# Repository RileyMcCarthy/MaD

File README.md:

# MaD — Low-Cost Open-Source Tensile Testing Machine

A relatively low-cost (**< $4,000**), portable, spray-resistant, user-modifiable,
open-source **uniaxial tensile testing machine** designed for low-modulus
elastomeric and biologic materials.

**📖 Documentation: <https://rileymccarthy.github.io/MaD/>** ·
**🚀 Run the control app: <https://rileymccarthy.github.io/MaD/app/>** (Chrome/Edge)

> The full guides — first-time setup, every UI screen with screenshots, the
> architecture, and developer/reference material — live on the
> [documentation site](https://rileymccarthy.github.io/MaD/). This README is the
> quick map.

## Specifications

| Parameter | Range |
|---|---|
| Strain Rate | 0 – 2 m/s |
| Force Measurement | 1 – 10 N |
| Gauge Length | 10 – 150 mm |
| Strain Length | 0 – 500 mm |
| Data Rate | 1000 samples/sec |

## The control app runs in your browser

The control app — **Control** — is a frontend-only Progressive Web App.
There is **nothing to install**: the browser talks straight to the Propeller 2
over the **Web Serial API**, and the protocol logic runs as **WebAssembly**
compiled from the same Rust core used by the firmware tooling and the test rig.

Open **<https://rileymccarthy.github.io/MaD/app/>** in Chrome or Edge, connect
over USB, and run a test. See the
[getting started guide](https://rileymccarthy.github.io/MaD/getting-started/).

> **Chromium-only:** Web Serial and the File System Access API are available only
> in Chrome/Edge on desktop.

## Repository structure

```
MaD/
├── Firmware/MaDCore/        Embedded C for the Propeller 2 (APP/DEV/IO/Library/HAL/HW)
├── Software/
│   └── Control/      Browser control app (Web Serial + WASM) — the app you ship
├── Protocol/                Schema + toolchain + Rust codec crate
│   ├── MaDProtocol.yaml     Single source-of-truth schema
│   ├── rust/                The `protocol` crate — generated Rust codec (SIL workspace member)
│   └── ProtoEmb/            ⎘ submodule → github.com/RileyMcCarthy/protoemb (YAML→C/TS/Rust codegen + runtime)
├── SIL/                     Software-in-the-loop test rig (Rust workspace)
│   ├── embsim/              ⎘ submodule → github.com/RileyMcCarthy/embsim (reusable SIL framework)
│   ├── models/              MaD physics models (gantry, sample, strain gauge)
│   ├── p2core/              The Propeller 2 instruction-set simulator (ISS)
│   ├── p2iss/               The ISS as an embsim component
│   ├── mad-catalog/         MaD's embsim kinds (carrier, add-on, ISS, machine); mad*.toml are the machine's projects
│   └── mad-runner/          The embsim command over MaD's kinds
├── Vibes/                   ⎘ submodule → github.com/RileyMcCarthy/vibes (behaviour ledger tool; the ledger is behaviours.jsonl)
├── Hardware/                KiCad PCB designs (EdgeBoard, DS2Addon)
└── docs/  +  mkdocs.yml     The documentation site
```

> Three components are **git submodules** (they are standalone open-source
> libraries): [`Protocol/ProtoEmb`](https://github.com/RileyMcCarthy/protoemb),
> [`SIL/embsim`](https://github.com/RileyMcCarthy/embsim) and
> [`Vibes`](https://github.com/RileyMcCarthy/vibes). Clone with
> `git clone --recurse-submodules`, or run
> `git submodule update --init --recursive` in an existing checkout.

## How it fits together

A single YAML schema (`Protocol/MaDProtocol.yaml`) generates the encode/decode
code for the firmware (C), the app (TypeScript + WASM), and the test rig (Rust),
so every layer agrees on the wire format byte-for-byte. The app and firmware speak
this **ProtoEmb** binary protocol over serial; motion profiles compile to G-code
that the firmware plays back from its SD card.

See [How it works](https://rileymccarthy.github.io/MaD/how-it-works/) for the
architecture with diagrams.

## Quick start

### Use the app
Open <https://rileymccarthy.github.io/MaD/app/> in Chrome/Edge — no install.

### Run the app from source
```bash
cd Software/Control
npm install
npm run build:wasm        # compile the Rust protocol core → src/wasm/
npm run generate:proto    # generate the TS codec from the YAML schema
npm run app               # opens your browser; connect on the control port via Web Serial
```

### Build the firmware
```bash
cd Firmware/MaDCore
pio run -e MaD                 # the firmware: hardware and the SIL run this image
pio run -e MaD -t upload       # flash a connected board through J1 (the programming port)
pio test -e native_test        # unit tests
pio check -e MaD --fail-on-defect=medium --fail-on-defect=high  # MISRA (medium+high)
```

The machine has two serial ports: the **control port** (the secondary serial on
P30/P32, J4 on the Edge carrier v0.3), which carries the protocol and never
resets the chip, and the **programming port** (J1, or the P2-EVAL's own USB),
whose DTR resets the chip for flashing and which carries the debug log.

### Run the full simulation (no hardware)
```bash
cd SIL
make test         # build the P2 image + the workspace, run the Rust test suite
make playground   # the machine's project + the app in a Chrome window on the board's clock
make e2e          # the e2e suite on the machine's project, mad-cosim.toml (SCENARIOS=… for a subset)
```

### Regenerate the protocol
After editing `Protocol/MaDProtocol.yaml`, regenerate all three targets so they
stay in lock-step (the firmware also regenerates its C target on every build):
```bash
# from repo root
python3 ./Protocol/ProtoEmb/core/generate.py --schema ./Protocol/MaDProtocol.yaml --target c  --output ./Firmware/MaDCore/src/Generated         --templates ./Protocol/ProtoEmb/core/templates
python3 ./Protocol/ProtoEmb/core/generate.py --schema ./Protocol/MaDProtocol.yaml --target ts --output ./Software/Control/src/protocol/generated --templates ./Protocol/ProtoEmb/core/templates
python3 ./Protocol/ProtoEmb/core/generate.py --schema ./Protocol/MaDProtocol.yaml --target rs --output ./Protocol/rust/src/generated          --templates ./Protocol/ProtoEmb/core/templates
```

## Documentation

| If you want to… | Go to |
|---|---|
| Set up a machine and run your first test | [Getting started](https://rileymccarthy.github.io/MaD/getting-started/) |
| Learn every screen | [User guide](https://rileymccarthy.github.io/MaD/user-guide/) |
| Understand the design | [How it works](https://rileymccarthy.github.io/MaD/how-it-works/) |
| Build & contribute | [Developer guide](https://rileymccarthy.github.io/MaD/dev/) |
| Look up the protocol / G-code / formats | [Protocol messages](https://rileymccarthy.github.io/MaD/dev/protocol-messages/) · [G-code](https://rileymccarthy.github.io/MaD/dev/gcode/) · [File formats](https://rileymccarthy.github.io/MaD/user-guide/file-formats/) |

To work on the docs locally:
```bash
pip install -r docs/requirements.txt
mkdocs serve     # http://127.0.0.1:8000
```

## CI/CD & releases

GitHub Actions builds and tests on every push/PR (`.github/workflows/ci.yml`) and
deploys the docs + app to GitHub Pages (`.github/workflows/pages.yml`). Releases
are cut with version tags:

```bash
Software/Control/scripts/release.sh patch --no-tag   # bump package.json, then PR
Software/Control/scripts/release.sh --publish        # tag origin/main as madcontrol-vX.Y.Z
git tag firmware-v1.0.0 && git push origin firmware-v1.0.0   # firmware binaries
git tag hardware-v1.0.0 && git push origin hardware-v1.0.0   # hardware manufacturing files
```

## License

MIT

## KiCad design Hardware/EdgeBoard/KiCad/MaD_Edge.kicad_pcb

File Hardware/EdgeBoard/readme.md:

# MaD EdgeBoard

The **EdgeBoard** is the main controller PCB for the MaD tensile tester. It hosts
the **Parallax Propeller 2** microcontroller and carries all of the machine's I/O.

The current design is **revision v0.3** (2026-10). The revision is printed on the
silkscreen ("Rev v0.3", under the MaD logo) and in every title block. Boards made
from earlier files carry no revision text; the changelog below lists what differs.

## What's on the board

- **Propeller 2** module socket (the firmware in
  [`Firmware/MaDCore`](../../Firmware/MaDCore) runs here). The machine uses a
  **P2-EC32MB** module; see [P2 module pins](#p2-module-pins).
- **Servo drive interface** (J21): isolated STEP/DIR line drivers, enable, ready.
- **Encoder input** (J20): isolated quadrature receiver for the drive's encoder.
- **Endstops** and the **door interlock** / e-stop chain (J11-J18, current-loop
  inputs through optocouplers).
- **Control port: J4.** The control app talks to the P2 on P30 (RX) / P32 (TX),
  isolated through IC2, at 2,000,000 baud. The carrier has no USB-to-serial chip
  of its own.
- **Programming port: J1.** A Parallax Prop Plug on J1 (P62/P63/RESn/GND,
  silkscreen `G|RES|RX|TX`) flashes the firmware and carries its debug log. It
  does not carry the protocol.
- Header for the [DS2 Addon](../DS2Addon/readme.md) force-gauge interface.

## Encoder input (J20) and its jumpers

U25 is a 5 V RS-422 receiver (AM26C32). Every channel has a header jumper that
ties its minus input to **ENC_REF**, a 2.5 V reference made from SC_5V by
R43/R44 (2.2 kΩ each) and decoupled by C31:

| Jumper | Ties | Channel | U25 pins | P2 pin |
|---|---|---|---|---|
| JP2 `A` | A- (J20.2) to ENC_REF | A | 2/1 | P9 |
| JP3 `B` | B- (J20.4) to ENC_REF | B | 6/7 | P10 |
| JP6 `Z` | Z- (J20.8) to ENC_REF | Z (index) | 14/15 | P12 |
| JP5 `ZI` | ZI- (J20.10) to ENC_REF | ZI | 10/9 | P11 |

R40/R41/R42 (2.2 kΩ) pull A+, B+ and Z+ up to SC_5V. ZI+ has no pull-up.

**Settings by encoder type** (the silkscreen between the jumpers reads
`OC: A B Z`, the three to fit for an open-collector encoder):

- **RS-422 line-driver encoder** (A/A-, B/B-, Z/Z-): leave **all four jumpers
  open**. Wire A±, B±, Z± (and ZI± if it has a second index) to J20, and its 0 V to
  J20.5. A shunt here would short the driver's minus output to ENC_REF, which ties
  all four minus legs together.
- **Single-ended NPN open-collector encoder** (A, B, Z; for example the Omron
  E6B2-CWZ6C and its clones, such as the Taiss on this machine): fit shunts on
  **JP2, JP3 and JP6**. Wire A to J20.1, B to J20.3, Z to J20.7, and the encoder 0 V
  to J20.5. Leave JP5 open.
  - The encoder must be a true open collector, with **no internal pull-up**. A
    "voltage output" NPN encoder pulls its outputs up to its own supply.
  - A, B and Z read **inverted** on P9/P10/P12. The output sinks while active, so
    the Z index pulse is **active-low** on P12 (inferred: the receiver output is
    low whenever the + input is below ENC_REF). Inverting both A and B keeps the
    count direction.
- **Single-ended push-pull 0/5 V (TTL) encoder:** as for open collector. The
  pull-ups are harmless. Fit JP5 too if a second index is wired to ZI+.
- **Not supported: any encoder whose outputs swing above 5 V.** That includes
  push-pull HTL outputs and voltage-output NPN outputs on a 12-24 V supply. The
  silkscreen under J25 reads `ENC OUT 5V MAX`.
  - U25's A/B inputs are rated -11 V to +14 V absolute maximum, with a ±7 V
    common-mode range (read: TI SLLS104M §5.1 and §5.3, p.4). A 24 V output
    exceeds that.
  - It also pushes current back into the drive's 5 V through the 2.2 kΩ
    pull-ups: (24 - 5) V / 2.2 kΩ = 8.6 mA per line (inferred).

**Encoder supply (J25, `VIN +V 0V`).** J20 has no supply pin; all ten pins are
used. The encoder side of the board has only SC_5V, which comes from the drive
through J21.1. J25 is a pass-through for an external supply:

- J25.1 `VIN`: the external supply, **at the voltage the encoder is rated for**.
  For example, the Taiss is reported to need at least 7 V, and a 5 V RS-422
  encoder needs 5 V.
  - VIN may be up to 30 V, F1's rating (read: LUTE 1206L datasheet, Revision 2020,
    p.2).
- J25.2 `+V`: to the encoder's V+, through F1 (PTC, 0.20 A hold).
- J25.3 `0V`: the supply 0 V, tied to the encoder ground (EN_GND).
- **Use a supply that is isolated from the carrier's V_IN.** J25.3 is EN_GND, the
  drive side of IC14/IC16. A supply shared with V_IN returns to the carrier's GND,
  which joins the two grounds and bypasses the isolators (inferred from the
  netlist: V_IN returns to GND).

The pin order keeps VIN and 0 V apart, so one stray shunt cannot short the supply.

**Load on the drive's 5 V (SC_5V, J21.1).** The carrier draws up to about 45 mA
from it (inferred: sum of datasheet maxima at 5.5 V). On top of that, U24 sources
whatever the drive's STEP/DIR inputs draw. Check the total against the drive's
5 V output rating; the repo does not record the drive model.

| Load | Max current | Source |
|---|---|---|
| U25 AM26C32 | 15 mA | SLLS104M §5.6, p.5 |
| IC16 side 1 | 8 mA | ISO6740 DC, SLLSFJ6G §7.10, p.13 |
| IC14 side 2 (ISO7741F) | 5.2 mA | SLLSEP4K §5.10, p.14 |
| U24 AM26LS31 (SO, no load) | 3 mA | SLLS114N, p.6 |
| R25 (SRDY pull-up, 1 kΩ) | 5.5 mA | while SRDY is low |
| R40-R42 (2.2 kΩ pull-ups), new in v0.3 | 7.5 mA | open-collector outputs all low |
| R43 + R44 (ENC_REF divider), new in v0.3 | 1.25 mA | |

## Loop inputs (J11-J18)

Each input is a current loop: the loop + pin feeds an NSI50010 10 mA regulator
(IC6-IC13) and an optocoupler LED.

**Supported loop supply: 5 V to 12 V (±5 %), up to 50 °C ambient.**

- **15 V and 24 V loops are not supported** on this board.
- A 5 V loop works: at 4.75 V it leaves at least 3.05 V across the regulator,
  against the 1.8 V it needs.
- The limit is a calculation, not yet a measurement. Bench-check it once (see
  [change 8](#8-loop-regulators-ic6-ic13-cathode-copper-and-a-supported-range)).

## P2 module pins

The P2-EC32MB brings P0-P39 and P58-P63 to its edge fingers. It does **not** bring
out P40-P57: fingers 55, 56, 59-67 and 69-77 are no-connects, and P40-P55 drive the
module's PSRAM.

Source: Parallax P2-EC32MB Rev B schematic, as transcribed in
`SIL/embsim/boards/netlists/p2_ec32mb.net`.

- **J24 (P40-P47, VIO_40_47) is dead** with an EC32MB. It only works with a plain
  P2-EC module.
- **J22 (P32-P39) works.** On v0.3, J22.3 (P32) also carries IC2's TX input; see
  change 6.
- P32 also reaches the module's J101, a 2-pad solder link to the TCXO option pin
  (read: `p2_ec32mb.net`). Leave J101 open.
- P38/P39 also drive the module's LED buffer.

## Ordering notes

- **J3 via-in-pad:** the P29/P30/P31 vias sit inside J3 pads 11/10/9 (0.3 mm
  drill). Order them **filled and capped** (IPC-4761 Type VII). The board's
  User.Drawings layer circles them and carries the same note below the outline.
  KiCad 9 has no per-via fill setting, so the order form must say it. All other
  vias are tented.
- **Shunts SH1-SH4** are BOM-only rows with no footprint and no CPL entry. Fit
  them by hand after assembly: JP1 always; JP2, JP3 and JP6 only for an
  open-collector encoder.
- **IC14 must be the F part.** On receipt, check that the top marking reads
  `ISO7741F` (read: SLLSEP4K package option addendum, p.38). LCSC's parametric
  text for C485810 says "Fail-safe output High Level", which contradicts TI.
- **Board thickness:** the stackup in `MaD_Edge.kicad_pcb` adds up to 4.69 mm
  (three 1.51 mm dielectrics). It predates v0.3. Order the real thickness, and
  check the STEP export against it.
- **J25 fit:** J25 sits between the J20 and J21 Micro-Fit headers, 0.045 mm from
  both courtyards (measured). Check that a 3-pin housing fits on J25 with both
  Micro-Fit receptacles mated before ordering.

## Revision v0.3 changelog

Each change cites the finding it fixes and the datasheet behind it. The findings
come from the SIL hardware review and from the review of this revision. Tags:
(measured) means checked on these files with KiCad 9.0.6; (read) gives a datasheet
section and page; (inferred) is a judgement.

### 1. IC14: default-low isolator and a pull-down on P6 (servo enable)

**Finding SRV-F6.** The drive enable must not float on while the P2 is in reset,
booting or being flashed. Neither the carrier nor the module pulls P6, and the
fitted IC14 (non-F) outputs high from an open or unpowered input.

- **IC14 is now an ISO7741FDWR** (LCSC C485810, confirmed as the F part).
  - Same pinout as before (read: TI SLLSEP4K Table 4-1, p.5).
  - The F suffix gives a **low** output when the input is open or side 1 is
    unpowered (read: SLLSEP4K Table 7-2, p.29).
- **R39, 10 kΩ from P6 to GND,** holds the enable request low until firmware drives
  P6.
  - On the PCB it sits by IC14 and joins the P6 trace at U29 through two vias.
  - Electrically it is the same net as IC14 pin 5 (inferred).
- With the F part, STEP and DIR (P8/P7) also rest low while the P2 is not driving
  them. Check the drive accepts this (inferred: a step input normally counts edges,
  not levels).
- **Bring-up checks** (not yet done):
  - Check the top marking (see [Ordering notes](#ordering-notes)).
  - With the drive powered, scope J21.7 (enable) while switching the carrier on.
    The outputs are undetermined while VCC1 is between 1.7 V and 2.25 V (read:
    SLLSEP4K Table 7-2 note 1, p.29), and R39 cannot cover that window. Record
    whether the enable glitches.

### 2. Q1: the fitted SOT-23 MMBT3904 pinout, and its base drive

**Finding SRV-F8-Q1.** Q1 was drawn as a TO-92 2N3904 (1 E, 2 B, 3 C), but the
fitted part is a SOT-23 MMBT3904 (1 B, 2 E, 3 C) (read: JSCJ MMBT3904 datasheet,
LCSC C20526, p.1). JP1's open-collector position therefore could never enable the
drive.

- The symbol is now `Transistor_BJT:MMBT3904` and the footprint `SOT-23`.
- The pads are re-netted: base to R24, emitter to EN_GND (new via), collector to
  JP1 pin 3.
- **R24 is now 4.7 kΩ** (was 43 kΩ; UNI-ROYAL 0603WAF4701T5E, LCSC C23162).
  - With 43 kΩ, IC14's OUTC gave Q1 about 77 µA of base current, which limits the
    open-collector enable to about 8 mA at hFE min 100 (read: SLLSEP4K §5.9 p.13,
    VOH ≥ 4.1 V; C20526 p.1, hFE).
  - 4.7 kΩ gives 0.7-1.0 mA. That keeps Q1 saturated at about 10 mA and in its
    active region up to about 70 mA (inferred: a forced gain of 10-14 at 10 mA,
    near the IC/IB = 10 at which the datasheet specifies VCE(sat); hFE min 100).
  - OUTC then sources at most 1 mA into the base, inside the -4 mA VOH test point
    (read: SLLSEP4K §5.9, p.13) and the ±15 mA absolute maximum (§5.1, p.6). In
    the `5V` position of JP1 that 1 mA adds to the drive's enable current.
  - The value is a judgement: the repo does not record the drive's enable-input
    current. Check it against the drive manual.

### 3. U25: a 5 V receiver and its own decoupling

**Finding ENC-F3.** The AM26LV32IDR is rated 3.0-3.6 V, but U25 runs from 5 V
(read: TI SLLS202H §6.3).

- **U25 is now an AM26C32IDR** (LCSC C36693).
  - Same pinout (read: TI SLLS104M Table 4-1, p.3).
  - VCC 4.5-5.5 V (read: §5.3, p.4).
  - VOH at least 3.8 V at -6 mA (read: §5.6, p.5), above IC16's 0.7 × VCC1 = 3.5 V
    input threshold at 5.0 V. At 5.5 V the threshold is 3.85 V, so meeting it then
    relies on IC16's input drawing only microamps (inferred).
  - The schematic keeps the AM26LV32xD symbol, since KiCad has no AM26C32 symbol
    and the pinout is identical.
  - Not an AM26LS32: its 2.7 V high is too low for IC16.
- **C30, 0.1 µF from U25.16 to EN_GND,** placed beside the pin.
  - It is 0402 (Samsung CL05B104KO5NNNC, LCSC C1525), the only size that fits
    between JP2 and U25 (measured: courtyard search).

### 4. U25 enables tied; the Z channel gets a receiver; JP4 removed

**Finding ENC-F5.** U25's G and ~G enables were wired to J20's Z+ and Z-, so they
needed a shunt on JP4 that the BOM did not list. The enable pins have no internal
pull (read: SLLS202H Fig 8-2).

- **G (pin 4) now goes to SC_5V and ~G (pin 12) to EN_GND,** so U25 is always
  enabled (read: SLLS104M Table 7-1, p.9).
- **Z+/Z- (J20.7/.8) now go to 4A/4B (pins 14/15).** Output 4Y goes through IC16
  channel D to P12.
- **JP4 is deleted.**

### 5. Encoder front end: a reference, not ground; pull-ups; supply pass-through

**Findings ENC-F4a and ENC-F4b.** With a minus input grounded, a 0-5 V
single-ended signal never reaches the -0.2 V differential low threshold. The Taiss
NPN open-collector encoder also had no pull-up and no supply.

- **JP2/JP3/JP5 now tie A-/B-/ZI- to ENC_REF instead of EN_GND.** Their values are
  now A_REF, B_REF and ZI_REF.
- **JP6 (Z_REF) is new.** It is the Z- reference jumper, placed where JP4 was.
- **ENC_REF = SC_5V/2,** from R43/R44 (2.2 kΩ) and C31 (0.1 µF).
  - A single-ended 0-5 V input then swings about ±2.5 V around the reference.
  - The receiver needs only ±0.2 V (read: SLLS104M §5.6, p.5).
  - Input resistance is at least 12 kΩ per input (read: ibid.). With all four
    reference jumpers fitted, the worst-case loading moves ENC_REF to about
    1.8-3.2 V. That still leaves more than 1 V of margin (inferred, worst-case
    divider arithmetic).
- **R40/R41/R42 (2.2 kΩ to SC_5V) pull A+, B+ and Z+ up.**
  - The E6B2-CWZ6C open-collector output sinks up to 35 mA with 0.4 V residual
    (read: Omron E6B2-C datasheet, Ratings/Characteristics).
  - A 2.2 kΩ pull-up draws 2.3 mA.
  - An RS-422 driver handles the extra 2.3 mA (inferred).
- **J25 + F1** form the encoder supply pass-through.
  - The decision, its limits and its reasons are in
    [Encoder input](#encoder-input-j20-and-its-jumpers): outputs no higher than
    5 V, VIN at the encoder's own rating, and a supply isolated from V_IN.
  - F1 is a LUTE 1206L020/30NR (LCSC C7542932, measured: LCSC product detail):
    0.20 A hold, 0.46 A trip, 30 V, R1max 2.7 Ω (read: LUTE 1206L datasheet,
    Revision 2020, p.2).
  - Its hold current is 0.12 A at 70 °C (read: ibid., p.6), above the 80 mA
    maximum of an E6B2-CWZ6C (read: Omron E6B2-C datasheet).
  - J25 is a 1×3 2.54 mm header, the same part as JP1.
- **The BOM now names the shunts.** SH1-SH4 are BOM-only rows (no footprint): one
  2.54 mm shunt each for JP1 (always fitted) and for JP2/JP3/JP6 (open-collector
  encoder only). The part is HCTL HC-JP254-1-65-CL-B-G0, LCSC C5380290.
- **New load on SC_5V:** up to 8.75 mA from R40-R44. The full budget is in
  [Encoder input](#encoder-input-j20-and-its-jumpers).

### 6. Pi link (IC2/J4): module pins that exist, and a 3.3 V Pi side

**Findings HOST-F2 and HOST-F5.**

**The pin problem:**

- IC2 sat on P52-P55, which the P2-EC32MB does not bring out (see
  [P2 module pins](#p2-module-pins)).
- Of the pins the EC32MB does bring out, only **P29, P30 and P31 are unused on the
  carrier** (measured: the v0.2 netlist and `p2_ec32mb.net`).
- Every other brought-out pin already goes to a circuit or to J22.
- IC2 has four channels, so the fourth uses **P32**, which J22.3 shares.

**The new mapping:**

| IC2 pin | Channel | Was | Now | J4 pin |
|---|---|---|---|---|
| 3 INA | P2 TX to Pi | P55 | **P32** (J3 finger 8, J22.3) | J4.2 RPI_TX |
| 4 INB | GPO to Pi | P54 | **P31** (finger 9) | J4.4 RPI_GPO |
| 5 OUTC | Pi TX to P2 RX | P53 | **P30** (finger 10) | J4.3 RPI_RX |
| 6 OUTD | GPI from Pi | P52 | **P29** (finger 11) | J4.5 RPI_GPI |

- **Why P32 carries an isolator input:** sharing a pin with an input is harmless.
  An ISO674x input draws at most 10 µA (read: SLLSFJ6G, p.12), so J22.3 still works
  as P32 (inferred).
- **Why not P33,** which reaches only J22 and would avoid the J101 note: moving
  INA there means another firmware and SIL re-pin for one solder link that is open
  unless someone bridges it (read: `p2_ec32mb.net`, J101 "2-pad solder link").
  This is a judgement; it can still move.
- **Via-in-pad:** J3 fingers 9-11 have no copper access other than a via in the
  pad. J22 sits 0.3 mm above them and a bus runs 0.4 mm below.
  - The three 0.5/0.3 mm vias sit inside those pads (measured).
  - They must be filled and capped; see [Ordering notes](#ordering-notes).

**The Pi side:**

- **The Pi side now runs from the Pi's 3.3 V.** RPI_5V is renamed RPI_3V3,
  including the In2 plane under J4, and the J4.1 silkscreen reads `3V3`.
  - ISO674x VCC2 range: 2.25-5.5 V (read: SLLSFJ6G §6.3, p.8).
  - Input threshold: 0.7 × VCC (read: p.12). At 3.3 V the Pi's 3.3 V TX meets it.
  - The outputs swing to 3.3 V, so a Pi GPIO never sees 5 V.
  - The `RPI_3V3` netclass pattern follows the rename (it stays in Power).
- **IC2 is the non-F ISO6742DWR (default high).** A default-low output would hold
  a UART line low, which reads as a break (read: SLLSFJ6G Table 9-2, p.31).
  - Its LCSC number was C2862403, which is the **ISO7742FDWR** (F, default low)
    (measured: LCSC product detail). Assembly would have fitted the F part. It is
    now **C5216407, the ISO6742DWR** (measured: LCSC product detail).
  - IC1 shared that LCSC number, so it changes too and drops its ISO7742FDWR
    alternate. Boards built from earlier files most likely carry the F part on
    IC1 (inferred from the BOM). Its outputs to J5/J6 (IGPO1/2) idle **high** with
    the non-F part while P26/P27 are undriven. The firmware does not use P24-P27
    (measured: no `HW_pins.h` entry).

### 7. J4 footprint restored

**Finding HOST-J4.** J4's footprint had lost its 43045-0618 mounting pads.

- J4 is back on `Molex_Micro-Fit_3.0_43045-0618_2x03-1MP_P3.00mm_Vertical`.
- Its two mounting tabs are numbered MP (not pin 7), as in 2023, and carry no net.
- The left tab is 0.525 mm from the nearest other copper, an RPI_GPO via
  (measured); DRC reports no clearance item.
- The DRC parity note "No pad found for pin 7 (SHIELD)" is the same as on v0.2.

### 8. Loop regulators IC6-IC13: cathode copper and a supported range

**Finding REST-F7d.** On 24 V loops the NSI50010s run over their power rating on
almost no copper.

**The rating** (read: onsemi NSI50010Y/D Rev 3, p.3):

- 208 mW at 25 °C on 100 mm² of 1 oz copper, derate 1.66 mW/°C (RθJA 600 °C/W).
- 347 mW on 300 mm², derate 2.8 mW/°C; 436 mW on 500 mm², derate 3.5 mW/°C.
- RψJL (junction to cathode lead) 196 °C/W on the 100 mm² board.
- Current: Ireg 7-13 mA (read: p.2).

**What v0.3 adds** for each part (measured: zone fill):

- **On F.Cu, a pour around the cathode pad**, so the lead sits in copper rather
  than on a trace: 12-23 mm².
- **The same cathode pour on B.Cu, In1 and In2**: 134-227 mm² on each layer.
  In1 and In2 were empty there.
- **Six 0.6/0.3 mm vias** join the layers (five on IC11, where a sixth would fall
  outside its pour).
- Copper per cathode net totals 422-696 mm² over the four layers. v0.2 had only the
  pads and a short trace, about 5 mm² per part.
- The pours use thermal reliefs on the U5-U8 through-hole pins and stay solid on
  the SMD pads and vias.
- Measured fill to fill, the inner pours are 5.8 mm from the GND/+3.3V planes,
  2.25 mm from EN_GND/SC_5V and 3.9 mm from GND_IO/5V_IO.

**Why not a series resistor:** a resistor cannot also keep 5 V loops working.

- At 5 V the regulator has 5 - 1.7 V (VO2631 LED VF max; read: Vishay 84732
  Rev 2.3, p.3) = 3.3 V.
- It needs 1.8 V for 80 % of its current (read: NSI50010Y/D p.2). That leaves at
  most about 1.5 V for a resistor, about 115 Ω at 13 mA.
- At 24 V that resistor removes only about 20 mW.
- The opto needs at least 5 mA (I_TH max; read: Vishay 84732 Rev 2.3, p.3).
- 24 V loops would need a per-loop 1.5-2 kΩ resistor with a solder-jumper bypass
  for 5 V loops. That is a layout change not made here.

**Supported range.** The worst-case loop power is (V_loop × 1.05 - 1.1 V) × 13 mA.

- 1.1 V is the LED's minimum VF at 10 mA (read: Vishay 84732 Rev 2.0, p.3). Rev 2.3
  gives no minimum, so this is a judgement.
- The copper is credited only as the datasheet's 100 mm² case. It is spread over
  four layers behind vias, so a better case is not proven (inferred).
- The supported limit keeps 10 °C below the computed maximum, to cover the via
  path (inferred).

| Loop supply (+5 %) | Worst-case power | Max ambient on the 100 mm² rating | Verdict |
|---|---|---|---|
| 12 V (12.6 V) | 150 mW | 60 °C | Supported up to 50 °C |
| 15 V (15.75 V) | 190 mW | 35 °C | Not supported |
| 24 V (25.2 V) | 313 mW | over 208 mW at 25 °C | Not supported |

**Bench check (not yet done).** Run a 12.6 V loop on IC6-IC13 for 30 minutes.
Measure each cathode lead with an IR thermometer at emissivity 0.9 on a treated
surface (read: NSI50010Y/D p.3 note).

- Pass: each lead rises no more than 70 °C above ambient (inferred:
  150 °C - 50 °C - 196 °C/W × 0.15 W).
- Record the result here.

### 9. Revision marking and silkscreen

- Title blocks on all three sheets and on the PCB read v0.3.
- The silkscreen reads "Rev v0.3" under the logo.
- The SERVO label moved up 2.2 mm to clear R43/R44/C31.
- New silkscreen:
  - `VIN +V 0V` at J25, and `ENC OUT 5V MAX` under it.
  - `OC: A B Z` between the encoder jumpers.
  - `3V3` at J4.1.
- Q1's reference is shown again (0.8 mm, between Q1 and R24).
- None of the v0.3 silkscreen overlaps a footprint outline or a pad (measured:
  DRC with the silk rules switched on in a scratch copy).

### 10. BOM fields

- The 0.1 µF 0603 row (22 parts) ordered LCSC C14663, the YAGEO
  CC0603KRX7R9BB104, 50 V X7R 0603 (measured: LCSC product detail).
  - Its MPN field named a Samsung 0402 part (CL05A104KA5NNNC) and its description
    said 6 V. Both now match the ordered part.
  - The DigiKey number that went with the Samsung MPN is cleared; it could not be
    checked.
- F1, SH1-SH4 and IC14 field changes are covered in changes 5 and 1.

### Not changed in v0.3 (still open)

- IC16's Value, MPN and LCSC fields still name three different parts (IC16-BOM).
- The J14/J16 Value fields are still swapped relative to the nets (REST-F7c).
- DS2 GPIO0-2 are not tied (REST-F9i).
- U24 3A/4A are open (good practice only).
- 24 V loop inputs (see change 8).

### Firmware and SIL follow-up

Done in the same PR (commit 94ed68d):

- `Firmware/MaDCore/src/HAL/Include/HW_pins.h`: `HW_PIN_RPI_TX` 55 → **32** and
  `HW_PIN_RPI_RX` 53 → **30**, with the SIL's host pins to match (since renamed
  `HW_PIN_MAIN_TX` / `HW_PIN_MAIN_RX`).

Still to do:

- `HW_pins.h`:
  - New: GPO on P31, GPI on P29.
  - The index channel on this board is P12 (Z, channel 4) and P11 (ZI, channel 3).
    The firmware names them the other way round.
- embsim's own `mad_edge` fixture (upstream) still needs the same re-export.

Done since (2026-11-01, MaD's SIL):

- `SIL/mad-catalog/netlists/mad_edge.net` re-exported from these files with
  KiCad 9's `kicad-cli`. This brought in:
  - JP4 removed, JP6 added.
  - Q1 pin order, and R24 = 4.7 kΩ.
  - U25 enables and channel 4.
  - The ENC_REF network.
  - IC2 on P29-P32.
  - The SC_5V loads.
  - IC14's GND2 on EN_GND (MaD #299).
- SIL tests that assumed a JP4 shunt updated.

## Working with the design

This is a [KiCad](https://www.kicad.org/) 9 project. Open the `.kicad_pro` in this
folder to view or edit the schematic and layout. Use KiCad 9: KiCad 10 rewrites
the files and renames pins.

Manufacturing outputs (Gerbers, BOM, interactive BOM, 3D models) are generated by
the hardware CI job (KiBot) and published on `hardware-v*` release tags. See the
[CI/CD docs](https://rileymccarthy.github.io/MaD/dev/ci-cd-and-releases/).

## Documentation

For how the board fits into the wider system, see the
[Hardware overview](https://rileymccarthy.github.io/MaD/how-it-works/hardware/) on
the documentation site.

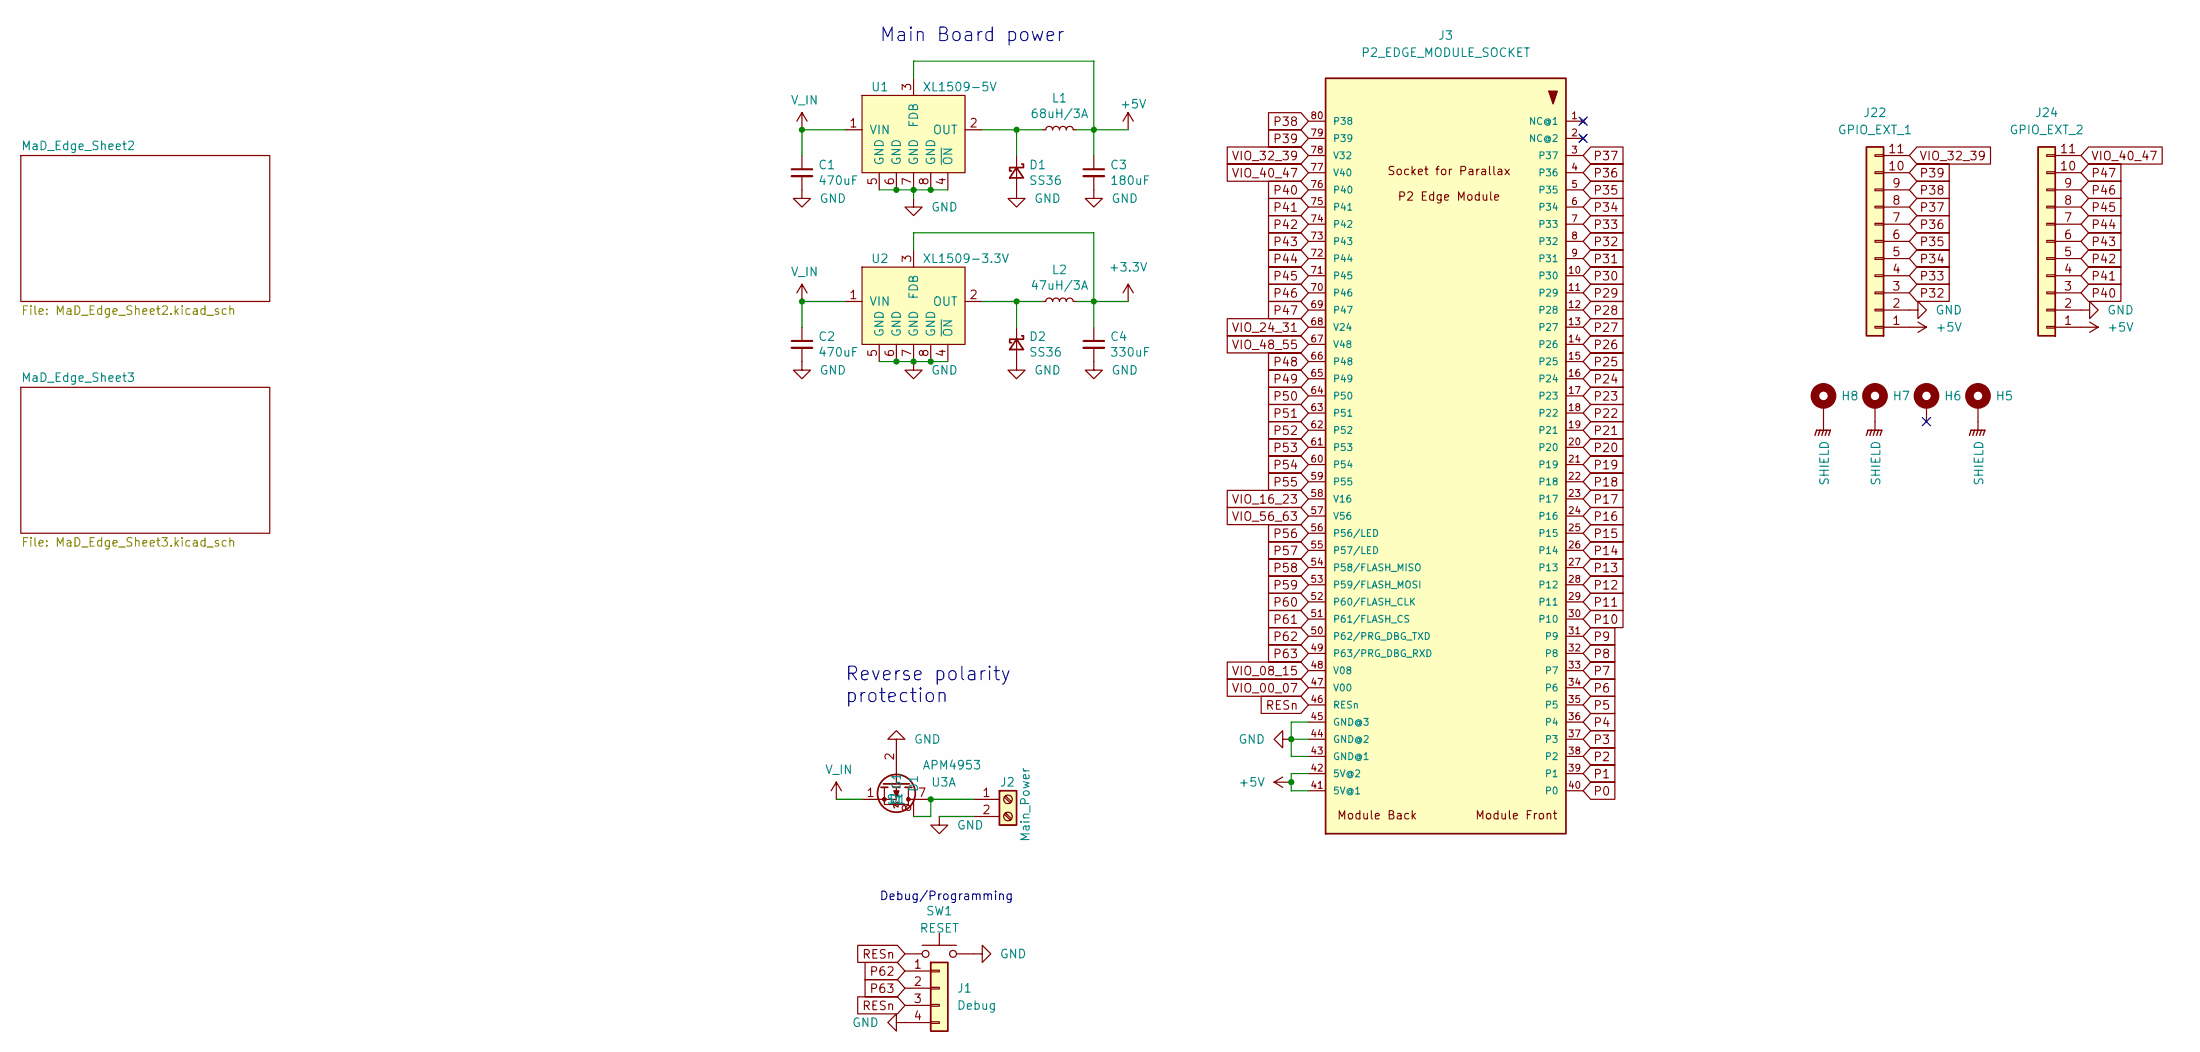
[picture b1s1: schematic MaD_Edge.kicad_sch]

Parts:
C1, C2: 470uF; C_Elec_10x10.2; Manufacturer_Part_Number EEH-ZS1E471P; DIGIKEY 10-EEH-ZS1E471PCT-ND
C3: 180uF; CP_Elec_8x6.9; Manufacturer_Part_Number 25SVPF180M; DIGIKEY P16510CT-ND
C4: 330uF; C_Elec_10x10.2; Manufacturer_Part_Number 25SVPF330M; DIGIKEY P16512CT-ND
D1, D2: SS36; D_SMC; Manufacturer_Part_Number SS36-E3/57T; DIGIKEY SS36-E3/57TGICT-ND
H5, H6, H7, H8: MountingHole_Pad; MountingHole_4mm_Pad; Manufacturer_Part_Number DNP; LCSC DNP
J1: Debug; PinHeader_1x04_P2.54mm_Vertical; Manufacturer_Part_Number DNP; LCSC DNP
J2: Main_Power; 705530106; Manufacturer_Part_Number 0705530106; DIGIKEY WM4153-ND
J3: P2_EDGE_MODULE_SOCKET; Card_Edge_SMT_VERT_1.27mm_80p; Manufacturer_Part_Number 450-00309; LCSC DNP
J22: GPIO_EXT_1; PinHeader_1x11_P1.27mm_Vertical; Manufacturer_Part_Number DNP; LCSC DNP
J24: GPIO_EXT_2; PinHeader_1x11_P1.27mm_Vertical; Manufacturer_Part_Number DNP; LCSC DNP
L1: 68uH/3A; L_10.4x10.4_H4.8; Manufacturer_Part_Number SRP1038A-470M; DIGIKEY SRP1038A-470MCT-ND
L2: 47uH/3A; L_10.4x10.4_H4.8; Manufacturer_Part_Number SLO1365H470MTT; LCSC C149548
SW1: RESET; SW_SPST_PTS645; manufacturer_part_numbe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 PTS645VK31LFS; LCSC C2804591
U1: XL1509-5V; SOP-8_3.9x4.9mm_P1.27mm; Manufacturer_Part_Number XL1509-5.0E1; LCSC C61063
U2: XL1509-3.3V; SOP-8_3.9x4.9mm_P1.27mm; Manufacturer_Part_Number XL1509-3.3E1; LCSC C74193
U3: APM4953; SOP-8_3.9x4.9mm_P1.27mm; Manufacturer_Part_Number APM4953KC-TRG; LCSC C20897

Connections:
+3.3V: C4.1, L2.2, U2.3 (FDB); also elsewhere on the board
+5V: C3.1, J3.41 (5V@1), J3.42 (5V@2), J22.1, J24.1, L1.2, U1.3 (FDB); also elsewhere on the board
GND: C1.2, C2.2, C3.2, C4.2, D1.2 (A), D2.2 (A), J1.4, J2.2, J3.43 (GND@1), J3.44 (GND@2), J3.45 (GND@3), J22.2, J24.2, SW1.2, U1.4 (~ON), U1.5 (GND), U1.6 (GND), U1.7 (GND), U1.8 (GND), U2.4 (~ON), U2.5 (GND), U2.6 (GND), U2.7 (GND), U2.8 (GND), U3.2 (G1); also elsewhere on the board
unnamed: D1.1 (K), L1.1, U1.2 (OUT)
unnamed: D2.1 (K), L2.1, U2.2 (OUT)
unnamed: J2.1, U3.7 (D1), U3.8 (D1)
P0: J3.40 (P0); also elsewhere on the board
P1: J3.39 (P1); also elsewhere on the board
P2: J3.38 (P2); also elsewhere on the board
P3: J3.37 (P3); also elsewhere on the board
P4: J3.36 (P4); also elsewhere on the board
P5: J3.35 (P5); also elsewhere on the board
P6: J3.34 (P6); also elsewhere on the board
P7: J3.33 (P7); also elsewhere on the board
P8: J3.32 (P8); also elsewhere on the board
P9: J3.31 (P9); also elsewhere on the board
P10: J3.30 (P10); also elsewhere on the board
P11: J3.29 (P11); also elsewhere on the board
P12: J3.28 (P12); also elsewhere on the board
P13: J3.27 (P13); also elsewhere on the board
P14: J3.26 (P14); also elsewhere on the board
P15: J3.25 (P15); also elsewhere on the board
P16: J3.24 (P16); also elsewhere on the board
P17: J3.23 (P17); also elsewhere on the board
P18: J3.22 (P18); also elsewhere on the board
P19: J3.21 (P19); also elsewhere on the board
P20: J3.20; also elsewhere on the board
P21: J3.19 (P21); also elsewhere on the board
P22: J3.18 (P22); also elsewhere on the board
P23: J3.17 (P23); also elsewhere on the board
P24: J3.16 (P24); also elsewhere on the board
P25: J3.15 (P25); also elsewhere on the board
P26: J3.14 (P26); also elsewhere on the board
P27: J3.13 (P27); also elsewhere on the board
P28: J3.12 (P28); also elsewhere on the board
P29: J3.11 (P29); also elsewhere on the board
P30: J3.10 (P30); also elsewhere on the board
P31: J3.9 (P31); also elsewhere on the board
P32: J3.8 (P32), J22.3; also elsewhere on the board
P33: J3.7 (P33), J22.4
P34: J3.6 (P34), J22.5
P35: J3.5 (P35), J22.6
P36: J3.4 (P36), J22.7
P37: J3.3 (P37), J22.8
P38: J3.80 (P38), J22.9
P39: J3.79 (P39), J22.10
P40: J3.76 (P40), J24.3
P41: J3.75 (P41), J24.4
P42: J3.74 (P42), J24.5
P43: J3.73 (P43), J24.6
P44: J3.72 (P44), J24.7
P45: J3.71 (P45), J24.8
P46: J3.70 (P46), J24.9
P47: J3.69 (P47), J24.10
P48: J3.66 (P48)
P49: J3.65 (P49)
P50: J3.64 (P50)
P51: J3.63 (P51)
P52: J3.62 (P52)
P53: J3.61 (P53)
P54: J3.60 (P54)
P55: J3.59 (P55)
P56: J3.56 (P56/LED)
P57: J3.55 (P57/LED)
P58: J3.54 (P58/FLASH_MISO)
P59: J3.53 (P59/FLASH_MOSI)
P60: J3.52 (P60/FLASH_CLK)
P61: J3.51 (P61/FLASH_CS)
P62: J1.1, J3.50 (P62/PRG_DBG_TXD)
P63: J1.2, J3.49 (P63/PRG_DBG_RXD)
RESn: J1.3, J3.46 (RESn), SW1.1
SHIELD: H5.1, H7.1, H8.1; also elsewhere on the board
VIO_00_07: J3.47 (V00)
VIO_08_15: J3.48 (V08)
VIO_16_23: J3.58 (V16); also elsewhere on the board
VIO_24_31: J3.68 (V24)
VIO_32_39: J3.78 (V32), J22.11
VIO_40_47: J3.77 (V40), J24.11
VIO_48_55: J3.67 (V48)
VIO_56_63: J3.57 (V56)
V_IN: C1.1, C2.1, U1.1 (VIN), U2.1 (VIN), U3.1 (S1)

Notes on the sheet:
Debug/Programming
Main Board power
Reverse polarity protection

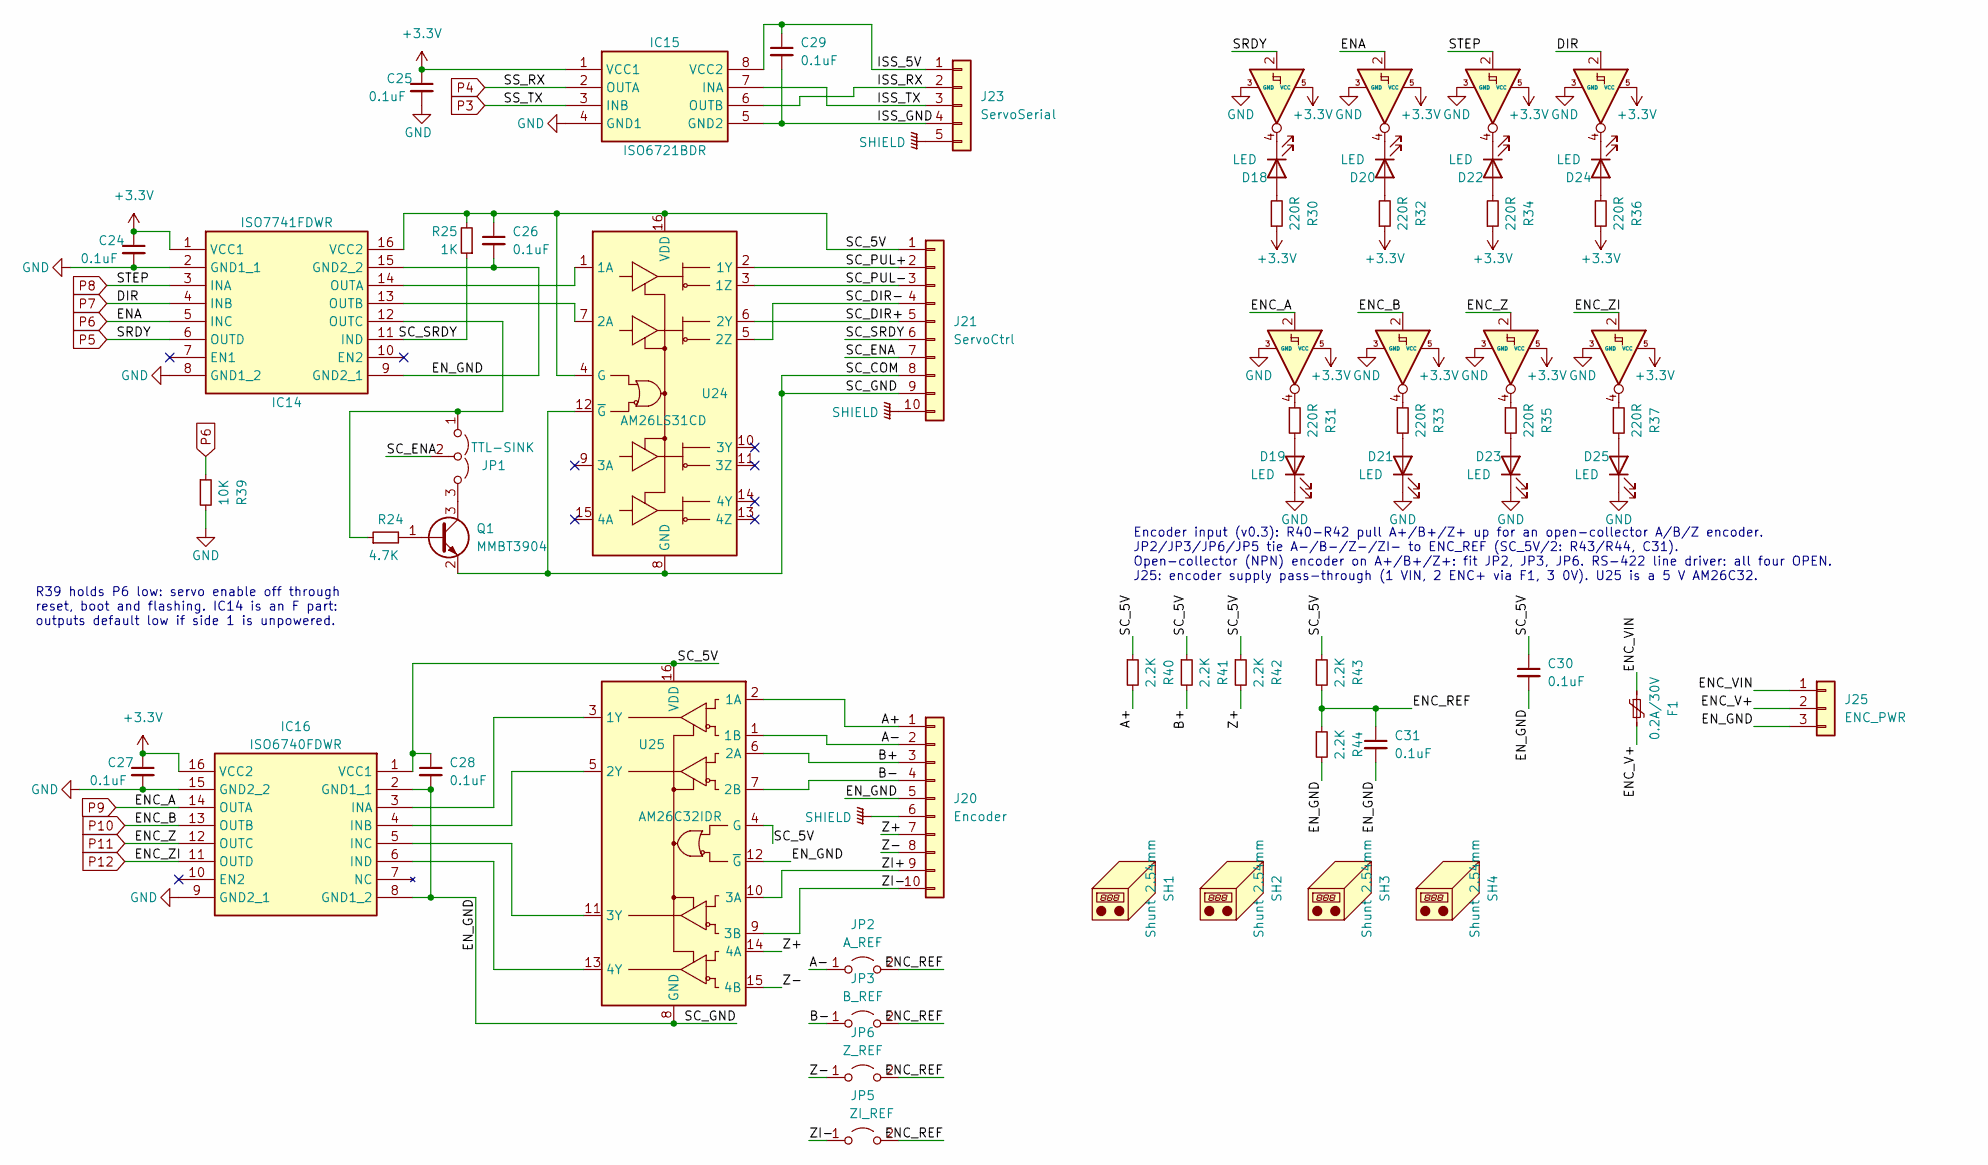
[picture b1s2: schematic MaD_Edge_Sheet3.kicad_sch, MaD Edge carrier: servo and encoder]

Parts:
C24, C25, C26, C27, C28, C29, C31: 0.1uF; C_0603_1608Metric; Manufacturer_Part_Number CL05A104KA5NNNC; DIGIKEY 1276-1043-1-ND
C30: 0.1uF; C_0402_1005Metric; Manufacturer_Part_Number CL05B104KO5NNNC; LCSC C1525
D18, D19, D20, D21, D22, D23, D24, D25: LED; LED_0603_1608Metric; Manufacturer_Part_Number LTST-C190KGKT; DIGIKEY 160-1435-1-ND
F1: 0.2A/30V; Fuse_1206_3216Metric; Manufacturer_Part_Number 1206L020/30NR; LCSC C7542932
IC14: ISO7741FDWR; SOIC127P1030X265-16N; Manufacturer_Part_Number ISO7741FDWR; LCSC C485810
IC15: ISO6721BDR; SOIC127P600X175-8N; Manufacturer_Part_Number ISO6721BDR; DIGIKEY 296-ISO6721BDRCT-ND
IC16: ISO6740FDWR; SOIC127P1030X265-16N; Manufacturer_Part_Number ISO6740DWR; DIGIKEY 296-ISO6740DWRCT-ND
J20: Encoder; Molex_Micro-Fit_3.0_43045-1015_2x05_P3.00mm_Vertical; Manufacturer_Part_Number 0430451015; DIGIKEY WM14304CT-ND
J21: ServoCtrl; Molex_Micro-Fit_3.0_43045-1015_2x05_P3.00mm_Vertical; Manufacturer_Part_Number 0430451015; DIGIKEY WM14304CT-ND
J23: ServoSerial; Molex_Micro-Fit_3.0_43650-0521_1x05_P3.00mm_Vertical; Manufacturer_Part_Number 0436500521; DIGIKEY WM14316CT-ND
J25: ENC_PWR; PinHeader_1x03_P2.54mm_Vertical; manufacturer_part_numbe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 PZ254V-11-03P; LCSC C2937625
JP1: TTL-SINK; PinHeader_1x03_P2.54mm_Vertical; manufacturer_part_numbe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 PZ254V-11-03P; LCSC C2937625
JP2: A_REF; PinHeader_1x02_P2.54mm_Vertical; manufacturer_part_numbe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 PZ254V-11-02P; LCSC C492401
JP3: B_REF; PinHeader_1x02_P2.54mm_Vertical; manufacturer_part_numbe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 PZ254V-11-02P; LCSC C492401
JP5: ZI_REF; PinHeader_1x02_P2.54mm_Vertical; manufacturer_part_numbe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 PZ254V-11-02P; LCSC C492401
JP6: Z_REF; PinHeader_1x02_P2.54mm_Vertical; manufacturer_part_numbe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 PZ254V-11-02P; LCSC C492401
Q1: MMBT3904; SOT-23; Manufacturer_Part_Number MMBT3904-TP; LCSC C20526
R24: 4.7K; R_0603_1608Metric; manufacturer_part_numbe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 0603WAF4701T5E; LCSC C23162
R25: 1K; R_0603_1608Metric; manufacturer_part_numbe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 0603WAF1001T5E; LCSC C21190
R30, R31, R32, R33, R34, R35, R36, R37: 220R; R_0603_1608Metric; manufacturer_part_numbe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 0603WAF2200T5E; LCSC C22962
R39: 10K; R_0603_1608Metric; Manufacturer_Part_Number 0603WAF1002T5E; LCSC C25804
R40, R41, R42, R43, R44: 2.2K; R_0603_1608Metric; Manufacturer_Part_Number 0603WAF2201T5E; LCSC C4190
SH1, SH2, SH3, SH4: Shunt 2.54mm; Manufacturer_Part_Number HC-JP254-1-65-CL-B-G0; LCSC C5380290
U24: AM26LS31CD; SOIC-16_3.9x9.9mm_P1.27mm; Manufacturer_Part_Number AM26LS31CD; LCSC C6179
U25: AM26C32IDR; SOIC-16_3.9x9.9mm_P1.27mm; Manufacturer_Part_Number AM26C32IDR; LCSC C36693
U27, U28, U29, U30, U31, U32, U33, U34: SN74LVC1G14DBV; SOT-23-5; Manufacturer_Part_Number SN74LVC1G14DBVT; LCSC C5250998

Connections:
+3.3V: C24.1, C25.1, C27.1, IC14.1 (VCC1), IC15.1 (VCC1), IC16.16 (VCC2), R30.1, R32.1, R34.1, R36.1, U27.5 (VCC), U28.5 (VCC), U29.5 (VCC), U30.5 (VCC), U31.5 (VCC), U32.5 (VCC), U33.5 (VCC), U34.5 (VCC); also elsewhere on the board
/MaD_Edge_Sheet3/A+: J20.1, R40.2, U25.2 (1A)
/MaD_Edge_Sheet3/A-: J20.2, JP2.1 (A), U25.1 (1B)
/MaD_Edge_Sheet3/B+: J20.3, R41.2, U25.6 (2A)
/MaD_Edge_Sheet3/B-: J20.4, JP3.1 (A), U25.7 (2B)
/MaD_Edge_Sheet3/ENC_REF: C31.1, JP2.2 (B), JP3.2 (B), JP5.2 (B), JP6.2 (B), R43.2, R44.1
/MaD_Edge_Sheet3/ENC_V+: F1.2, J25.2
/MaD_Edge_Sheet3/ENC_VIN: F1.1, J25.1
/MaD_Edge_Sheet3/EN_GND: C26.2, C28.2, C30.2, C31.2, IC14.9 (GND2_1), IC14.15 (GND2_2), IC16.2 (GND1_1), IC16.8 (GND1_2), J20.5, J21.8, J21.9, J25.3, Q1.2 (E), R44.2, U24.8 (GND), U24.12 (~G), U25.8 (GND), U25.12 (~G)
/MaD_Edge_Sheet3/ISS_5V: C29.1, IC15.8 (VCC2), J23.1
/MaD_Edge_Sheet3/ISS_GND: C29.2, IC15.5 (GND2), J23.4
/MaD_Edge_Sheet3/ISS_RX: IC15.6 (OUTB), J23.2
/MaD_Edge_Sheet3/ISS_TX: IC15.7 (INA), J23.3
/MaD_Edge_Sheet3/SC_5V: C26.1, C28.1, C30.1, IC14.16 (VCC2), IC16.1 (VCC1), J21.1, R25.2, R40.1, R41.1, R42.1, R43.1, U24.4 (G), U24.16 (VDD), U25.4 (G), U25.16 (VDD)
/MaD_Edge_Sheet3/SC_DIR+: J21.5, U24.6 (2Y)
/MaD_Edge_Sheet3/SC_DIR-: J21.4, U24.5 (2Z)
/MaD_Edge_Sheet3/SC_ENA: J21.7, JP1.2 (C)
/MaD_Edge_Sheet3/SC_PUL+: J21.2, U24.2 (1Y)
/MaD_Edge_Sheet3/SC_PUL-: J21.3, U24.3 (1Z)
/MaD_Edge_Sheet3/SC_SRDY: IC14.11 (IND), J21.6, R25.1
/MaD_Edge_Sheet3/Z+: J20.7, R42.2, U25.14 (4A)
/MaD_Edge_Sheet3/Z-: J20.8, JP6.1 (A), U25.15 (4B)
/MaD_Edge_Sheet3/ZI+: J20.9, U25.10 (3A)
/MaD_Edge_Sheet3/ZI-: J20.10, JP5.1 (A), U25.9 (3B)
GND: C24.2, C25.2, C27.2, D19.1 (K), D21.1 (K), D23.1 (K), D25.1 (K), IC14.2 (GND1_1), IC14.8 (GND1_2), IC15.4 (GND1), IC16.9 (GND2_1), IC16.15 (GND2_2), R39.2, U27.3 (GND), U28.3 (GND), U29.3 (GND), U30.3 (GND), U31.3 (GND), U32.3 (GND), U33.3 (GND), U34.3 (GND); also elsewhere on the board
unnamed: D18.2 (A), R30.2
unnamed: D18.1 (K), U27.4
unnamed: D19.2 (A), R31.2
unnamed: D20.2 (A), R32.2
unnamed: D20.1 (K), U29.4
unnamed: D21.2 (A), R33.2
unnamed: D22.2 (A), R34.2
unnamed: D22.1 (K), U31.4
unnamed: D23.2 (A), R35.2
unnamed: D24.2 (A), R36.2
unnamed: D24.1 (K), U33.4
unnamed: D25.2 (A), R37.2
unnamed: IC14.14 (OUTA), U24.1 (1A)
unnamed: IC14.13 (OUTB), U24.7 (2A)
unnamed: IC14.12 (OUTC), JP1.1 (A), R24.1
unnamed: IC16.3 (INA), U25.3 (1Y)
unnamed: IC16.4 (INB), U25.5 (2Y)
unnamed: IC16.5 (INC), U25.11 (3Y)
unnamed: IC16.6 (IND), U25.13 (4Y)
unnamed: JP1.3 (B), Q1.3 (C)
unnamed: Q1.1 (B), R24.2
unnamed: R31.1, U28.4
unnamed: R33.1, U30.4
unnamed: R35.1, U32.4
unnamed: R37.1, U34.4
P3: IC15.3 (INB); also elsewhere on the board
P4: IC15.2 (OUTA); also elsewhere on the board
P5: IC14.6 (OUTD), U27.2; also elsewhere on the board
P6: IC14.5 (INC), R39.1, U29.2; also elsewhere on the board
P7: IC14.4 (INB), U33.2; also elsewhere on the board
P8: IC14.3 (INA), U31.2; also elsewhere on the board
P9: IC16.14 (OUTA), U28.2; also elsewhere on the board
P10: IC16.13 (OUTB), U30.2; also elsewhere on the board
P11: IC16.12 (OUTC), U32.2; also elsewhere on the board
P12: IC16.11 (OUTD), U34.2; also elsewhere on the board
SHIELD: J20.6, J21.10, J23.5; also elsewhere on the board

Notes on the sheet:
R39 holds P6 low: servo enable off through reset, boot and flashing. IC14 is an F part: outputs default low if side 1 is unpowered.
Encoder input (v0.3): R40-R42 pull A+/B+/Z+ up for an open-collector A/B/Z encoder. JP2/JP3/JP6/JP5 tie A-/B-/Z-/ZI- to ENC_REF (SC_5V/2: R43/R44, C31). Open-collector (NPN) encoder on A+/B+/Z+: fit JP2, JP3, JP6. RS-422 line driver: all four OPEN. J25: encoder supply pass-through (1 VIN, 2 ENC+ vi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
